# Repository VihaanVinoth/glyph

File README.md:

# glyph
Simple stenographic keyboard

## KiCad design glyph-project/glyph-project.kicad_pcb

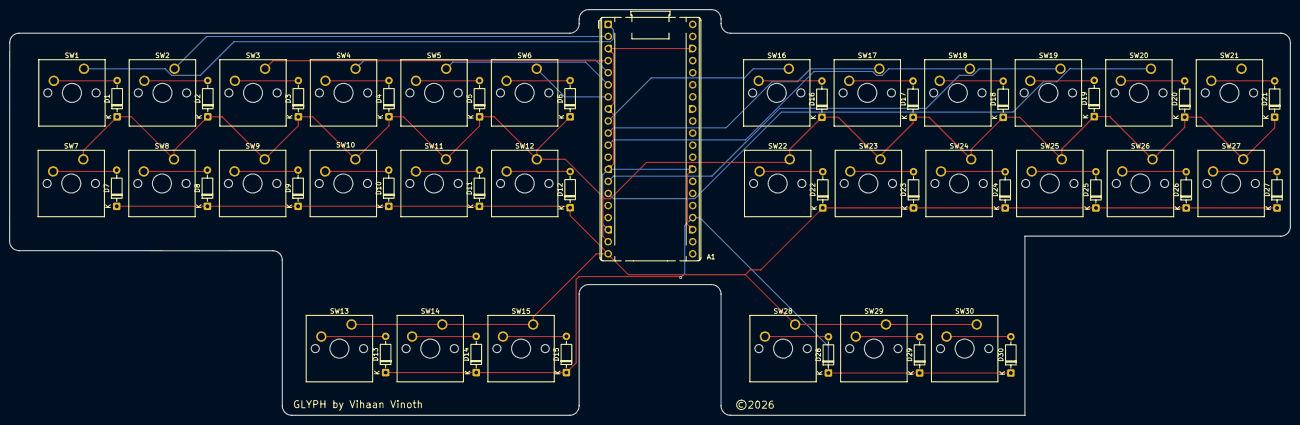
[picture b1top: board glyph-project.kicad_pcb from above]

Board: 2 copper layers, 269.5 x 85.4 mm, 61 parts (0 on the bottom side), 45 nets.

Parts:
A1: RaspberryPi_Pico; RaspberryPi_Pico_Common_THT
D1, D2, D3, D4, D5, D6, D7, D8, D9, D10, D11, D12, D13, D14, D15, D16, D17, D18, D19, D20, D21, D22, D23, D24, D25, D26, D27, D28, D29, D30: 1N4148; D_DO-35_SOD27_P7.62mm_Horizontal
SW1, SW2, SW3, SW4, SW5, SW6, SW7, SW8, SW9, SW10, SW11, SW12, SW13, SW14, SW15, SW16, SW17, SW18, SW19, SW20, SW21, SW22, SW23, SW24, SW25, SW26, SW27, SW28, SW29, SW30: SW_Push_45deg; SW_Cherry_MX_1.00u_PCB

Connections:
COL0: A1.1 (GPIO0), SW1.1
COL1: A1.2 (GPIO1), SW2.1
COL2: A1.4 (GPIO2), SW3.1
COL3: A1.5 (GPIO3), SW4.1
COL4: A1.6 (GPIO4), SW5.1
COL5: A1.7 (GPIO5), SW6.1
COL6: A1.9 (GPIO6), SW16.1
COL7: A1.10 (GPIO7), SW17.1
COL8: A1.11 (GPIO8), SW18.1
COL10: A1.14 (GPIO10), SW19.1
COL11: A1.15 (GPIO11), SW20.1
GND: A1.3 (GND), A1.8 (GND), A1.13 (GND), A1.18 (GND), A1.23 (GND), A1.28 (GND), A1.38 (GND)
unnamed: D1.2 (A), SW1.2
unnamed: D2.2 (A), SW2.2
unnamed: D3.2 (A), SW3.2
unnamed: D4.2 (A), SW4.2
unnamed: D5.2 (A), SW5.2
unnamed: D6.2 (A), SW6.2
unnamed: D7.2 (A), SW7.2
unnamed: D8.2 (A), SW8.2
unnamed: D9.2 (A), SW9.2
unnamed: D10.2 (A), SW10.2
unnamed: D11.2 (A), SW11.2
unnamed: D12.2 (A), SW12.2
unnamed: D13.2 (A), SW13.2
unnamed: D14.2 (A), SW14.2
unnamed: D15.2 (A), SW15.2
unnamed: D16.2 (A), SW16.2
unnamed: D17.2 (A), SW17.2
unnamed: D18.2 (A), SW18.2
unnamed: D19.2 (A), SW19.2
unnamed: D20.2 (A), SW20.2
unnamed: D21.2 (A), SW21.2
unnamed: D22.2 (A), SW22.2
unnamed: D23.2 (A), SW23.2
unnamed: D24.2 (A), SW24.2
unnamed: D25.2 (A), SW25.2
unnamed: D26.2 (A), SW26.2
unnamed: D27.2 (A), SW27.2
unnamed: D28.2 (A), SW28.2
unnamed: D29.2 (A), SW29.2
unnamed: D30.2 (A), SW30.2
ROW0: A1.19 (GPIO14), D1.1 (K), D2.1 (K), D3.1 (K), D4.1 (K), D5.1 (K), D6.1 (K), D16.1 (K), D17.1 (K), D18.1 (K), D19.1 (K), D20.1 (K), D21.1 (K), SW7.1, SW8.1, SW9.1, SW10.1, SW11.1, SW12.1, SW22.1, SW23.1, SW24.1, SW25.1, SW26.1, SW27.1
ROW1: A1.20 (GPIO15), D7.1 (K), D8.1 (K), D9.1 (K), D10.1 (K), D11.1 (K), D12.1 (K), D22.1 (K), D23.1 (K), D24.1 (K), D25.1 (K), D26.1 (K), D27.1 (K), SW13.1, SW14.1, SW15.1, SW28.1, SW29.1, SW30.1
ROW2: A1.24 (GPIO18), D13.1 (K), D14.1 (K), D15.1 (K), D28.1 (K), D29.1 (K), D30.1 (K)

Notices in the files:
glyph-project/glyph-project.kicad_pcb:
©2026
